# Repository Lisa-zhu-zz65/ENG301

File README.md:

# Music Bracelet Project
Repository for the music bracelet project, with hardware and software work detailed. \
Project_1 folder contains all the files created and used in the music bracelet prototype.\
Project_2 folder contains all the files created for the music bracelet PCB design.

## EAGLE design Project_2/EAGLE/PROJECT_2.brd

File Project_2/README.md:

This folder contains all information about the PCB design of the Music Bracelet Project.

The Project Proposal, bottom and top layer layouts are in the docs folder; the implementation files are in the EAGLE folder; the manufacturing files are in the MFG folder; the schematics is in this folder.

For more information about the project, check the Project_1 folder.

Built on pocketbeagle with python, this bracelet can provide combined effects of vibration and LED while playing music. Please visit for a complete tutorial and build instructions.

Libraries to install: -speaker: sudo apt-get update sudo apt-get install alsa-utils libasound2 -y sudo apt-get install mplayer -y -SPI screen: sudo apt get update sudo pip3 install upgrade Pillow sudo pip3 install adafruit circuitpython busdevice sudo pip3 install adafruit circuitpython rgb display sudo apt get install ttf dejavu y -LED Strip: download the files in the LED_Strip folder

Implementation Files: In Project_1/LED_Strip, do ./run, this will connect the opc server of the LED strip; Open another terminal, in Project_2/SPI_screen, do ./run, this will start the program.

To autoboot the system, use sudo crontab -e, and add two lines: @reboot sleep 30 && sh /var/lib/cloud9/ENGI301/Project_1/LED_Strip/run > /var/lib/cloud9/ENGI301/Project_1/LED/log/cronlog 2>&1 @reboot sleep 30 && sh /var/lib/cloud9/ENGI301/Project_1/SPI_screen/run > /var/lib/cloud9/ENGI301/Project_1/SPI_screen/log/cronlog 2>&1

Instructions for use:

Clone the repository in /var/lib/cloud9 of PocketBeagle
Assemble the system according to the hackster page
Run the system using two run files
Enjoy the bracelet!

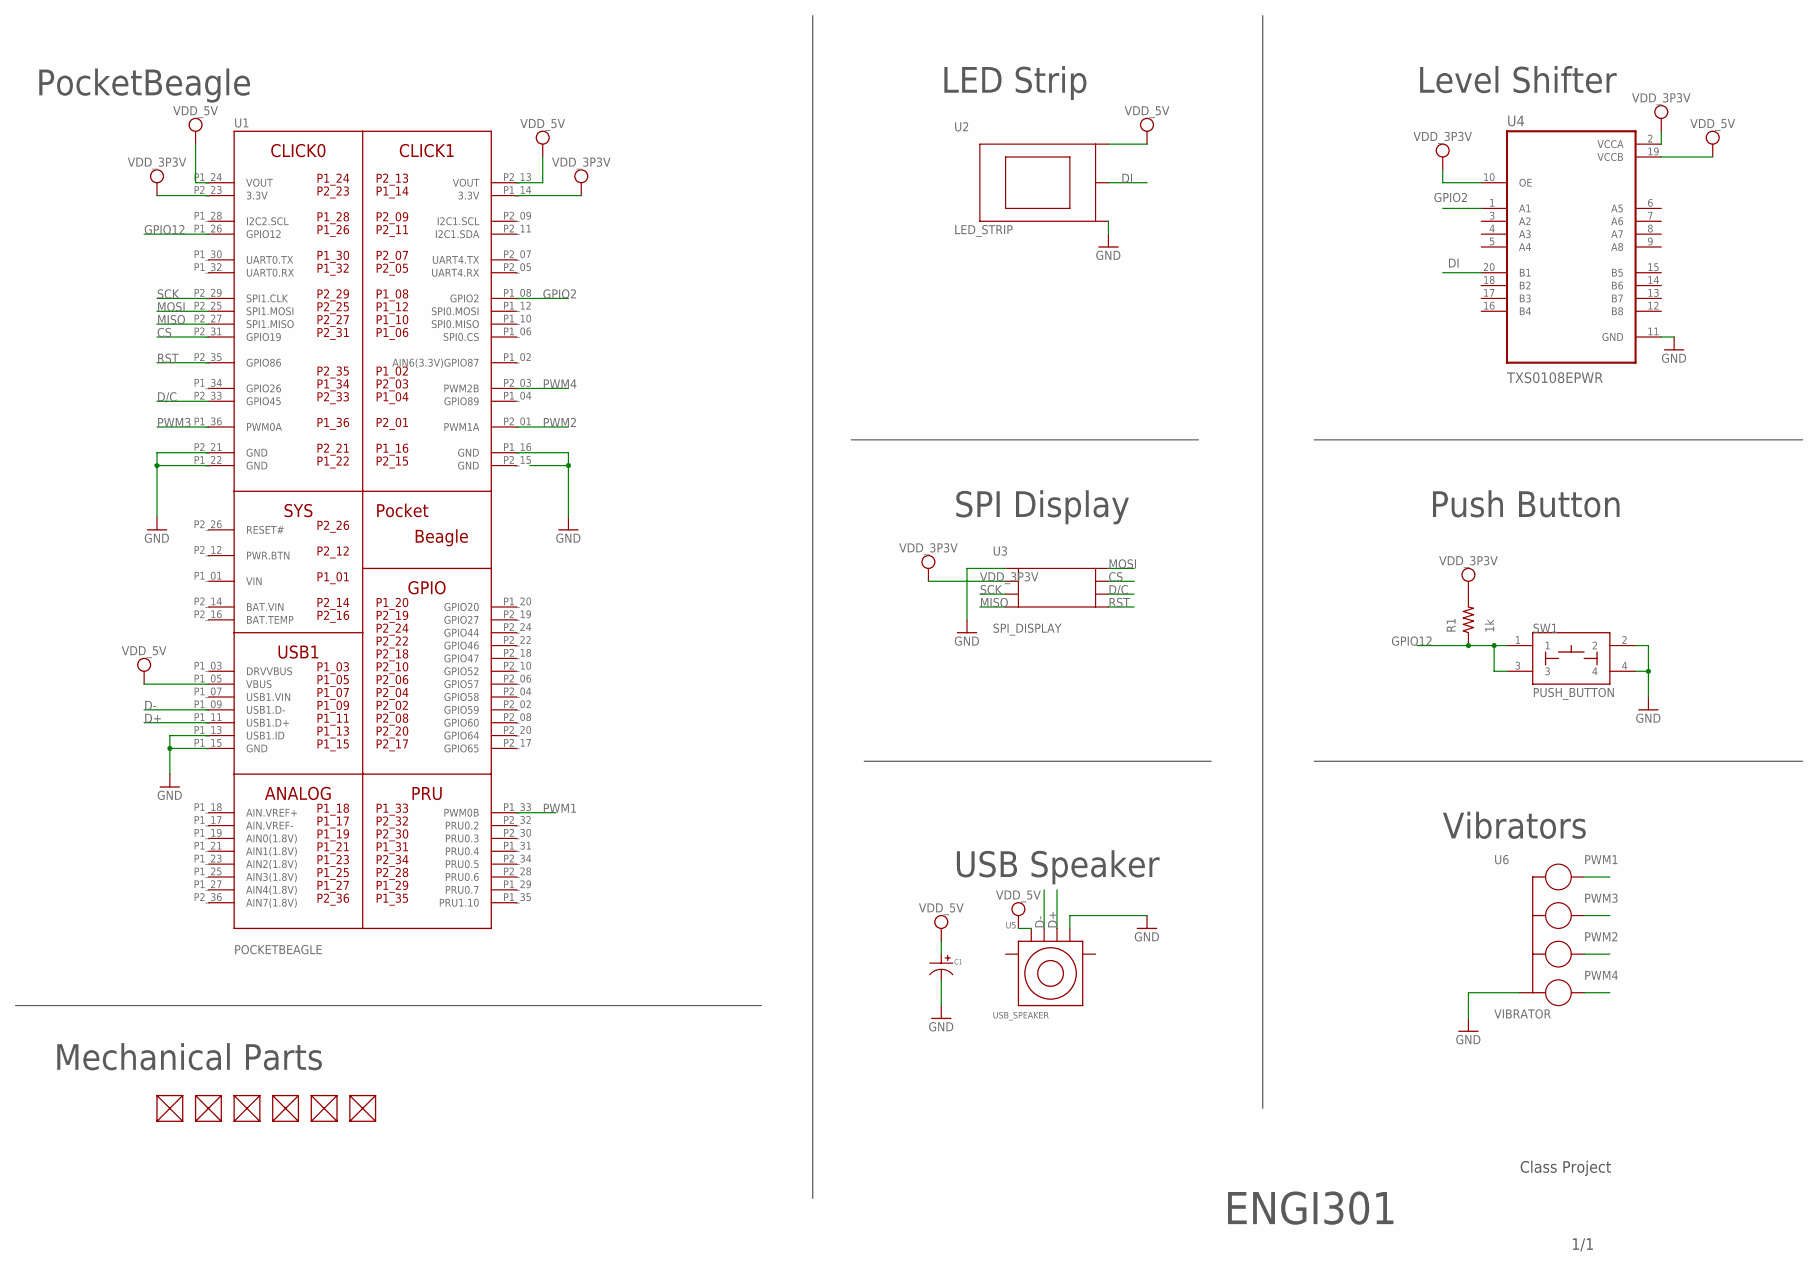
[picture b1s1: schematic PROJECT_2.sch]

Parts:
C1: CAPACITOR_P_10MM; CP10MM
FUD1, FUD2, FUD3, FUD4, FUD5, FUD6: FIDUCIAL; FIDUCIAL_40MIL
R1: 1k; R0603
SW1: PUSH_BUTTON; BUTTON_12.5MM
U1: POCKETBEAGLE
U2: LED_STRIP; LED_HEADERS
U3: SPI_DISPLAY
U4: TXS0108EPWR; SOP65P640X120-20N
U5: USB_SPEAKER; USB_CONNECTOR
U6: VIBRATOR; VIBRATOR_HEADERS

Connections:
BAT.VIN: U1.P2_14 (BAT.VIN)
CS: U1.P2_31 (GPIO19), U3.TFT-CS (CS)
D+: U1.P1_11 (USB1.D+), U5.D+
D-: U1.P1_09 (USB1.D-), U5.D-
D/C: U1.P2_33 (GPIO45), U3.D/C
DI: U2.SIG, U4.20 (B1)
GND: C1.P$2, SW1.2, SW1.4, U1.P1_13 (USB1.ID), U1.P1_15 (GND), U1.P1_16 (GND), U1.P1_22 (GND), U1.P2_15 (GND), U1.P2_21 (GND), U2.GND, U3.GND, U4.11 (GND), U5.GND, U6.GND
GPIO2: U1.P1_08 (GPIO2), U4.1 (A1)
GPIO12: R1.1, SW1.1, SW1.3, U1.P1_26 (GPIO12)
MISO: U1.P2_27 (SPI1.MISO), U3.MISO
MOSI: U1.P2_25 (SPI1.MOSI), U3.MOSI
PWM1: U1.P1_33 (PWM0B), U6.PWM1
PWM2: U1.P2_01 (PWM1A), U6.PWM3
PWM3: U1.P1_36 (PWM0A), U6.PWM2
PWM4: U1.P2_03 (PWM2B), U6.PWM4
RST: U1.P2_35 (GPIO86), U3.RST
SCK: U1.P2_29 (SPI1.CLK), U3.SCK
VDD_3P3V: R1.2, U1.P1_14 (3.3V), U1.P2_23 (3.3V), U3.VCC, U4.2 (VCCA), U4.10 (OE)
VDD_5V: C1.P$1, U1.P1_05 (VBUS), U1.P1_24 (VOUT), U1.P2_13 (VOUT), U2.PWR (VIN), U4.19 (VCCB), U5.VBUS
VIN: U1.P1_01 (VIN)

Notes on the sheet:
PocketBeagle
LED Strip
Level Shifter
SPI Display
Push Button
Vibrators
USB Speaker
Mechanical Parts
ENGI301
1/1
Class Project

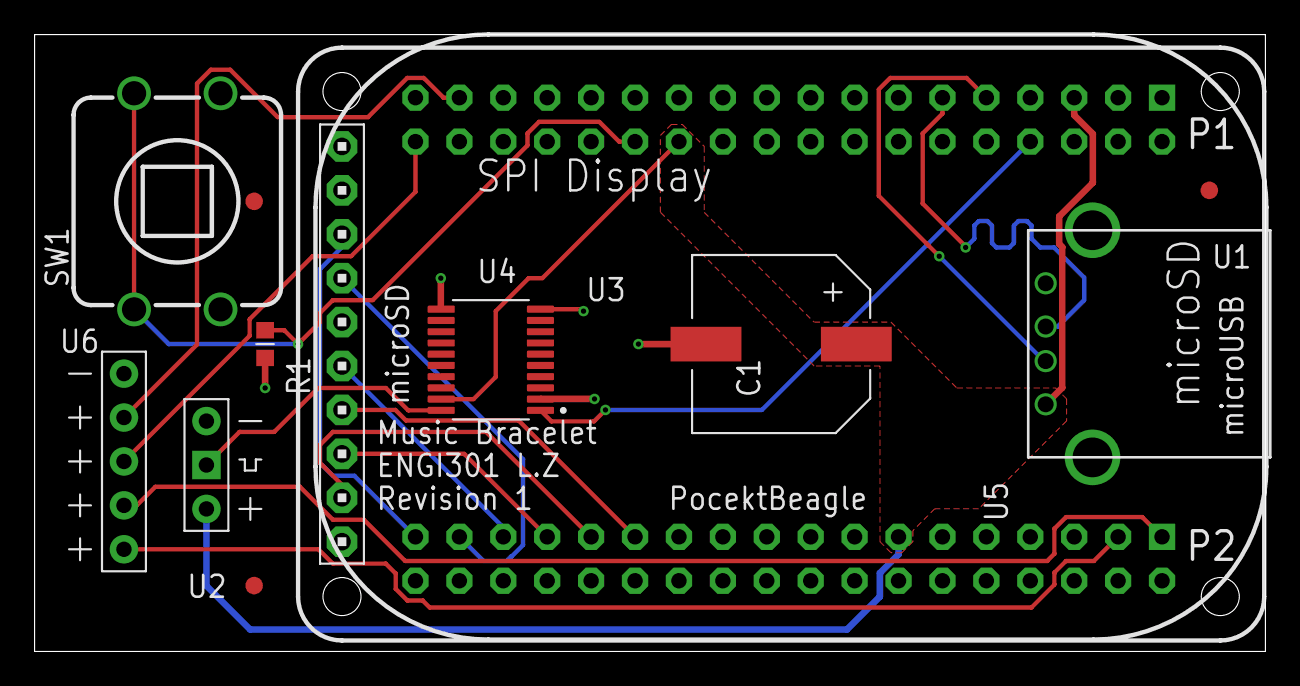
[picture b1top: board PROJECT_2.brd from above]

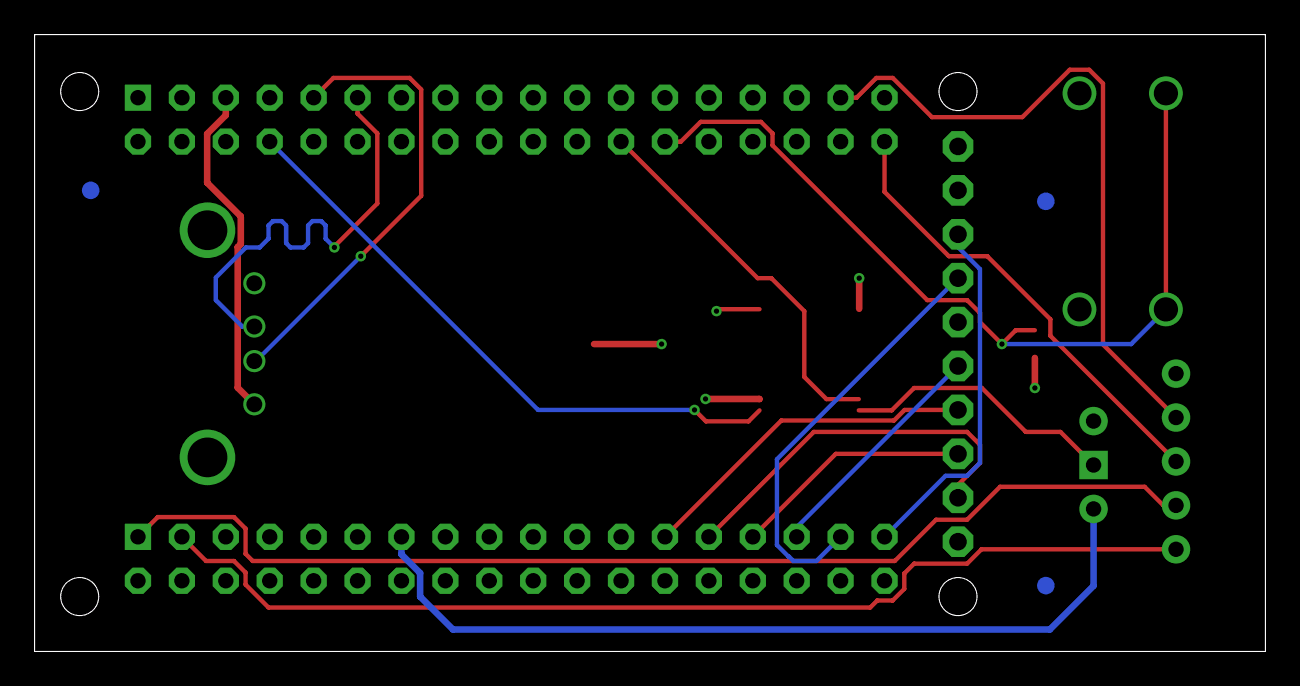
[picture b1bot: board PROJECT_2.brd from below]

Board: 4 copper layers, 71.2 x 35.7 mm, 15 parts (3 on the bottom side), 18 nets.

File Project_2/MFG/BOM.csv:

"Qty";"Value";"Device";"Package";"Parts";"Description";"AVAILABILITY";"DESCRIPTION";"HOUSEPART";"MF";"MP";"MPN";"PACKAGE";"POPULATE";"PRICE";"PURCHASE-URL";"TOLERANCE";"URL";"VOLTAGE";
"1";"";"CAPACITOR_P_10MM";"CP10MM";"C1";"Library:  MF_Passives";"";"";"";"";"";"";"";"1";"";"";"";"";"";
"1";"1k";"R_R0603";"R0603";"R1";"RESISTOR, American symbol";"";"";"";"";"";"";"";"";"";"";"";"";"";
"6";"FIDUCIAL";"FIDUCIAL";"FIDUCIAL_40MIL";"FUD1, FUD2, FUD3, FUD4, FUD5, FUD6";"";"";"";"";"";"";"";"";"";"";"";"";"";"";
"1";"LED_STRIP";"LED_STRIP";"LED_HEADERS";"U2";"LED Strip";"";"";"";"";"";"";"";"";"";"";"";"";"";
"1";"POCKETBEAGLE";"POCKETBEAGLE";"POCKETBEAGLE";"U1";"";"";"";"";"";"";"";"";"";"";"";"";"";"";
"1";"PUSH_BUTTON";"PUSH_BUTTON";"BUTTON_12.5MM";"SW1";"";"";"";"";"";"";"";"";"";"";"";"";"";"";
"1";"SPI_DISPLAY";"SPI_DISPLAY";"SPI_DISPLAY";"U3";"1.8" Color TFT LCD display";"";"";"";"";"";"";"";"";"";"";"";"";"";
"1";"TXS0108EPWR";"TXS0108EPWR";"SOP65P640X120-20N";"U4";"Check prices";"In Stock";" 8-bit bidirectional voltage-level shifter for open-drain and push-pull application 20-TSSOP -40 to 85 ";"";"Texas Instruments";"TXS0108EPWR";"";"TSSOP-20 Texas Instruments";"";"None";"https://pricing.snapeda.com/search/part/TXS0108EPWR/?ref=eda";"";"";"";
"1";"USB_SPEAKER";"USB_SPEAKER";"USB_CONNECTOR";"U5";"";"";"";"";"";"";"";"";"";"";"";"";"";"";
"1";"VIBRATOR";"VIBRATOR";"VIBRATOR_HEADERS";"U6";"Vibration motor";"";"";"";"";"";"";"";"";"";"";"";"";"";

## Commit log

2021-10-05 Create simple_calc_class.py
    simple calc base file
2021-10-05 Create simple_calc_HW.py
    add left shift, right shift, power, modulo, and compatible with python 2 input
2021-10-05 add name to description
2021-10-05 Create blink_USR3.py
    add blink user LED 5 hz file
2021-10-14 Create Zhu_ENGI301_project_proposal.pptx
    add project proposal
2021-11-06 Add files via upload
    wave file aimer
2021-11-06 update project1
2021-11-09 update project files
2021-12-09 Project_2 files
